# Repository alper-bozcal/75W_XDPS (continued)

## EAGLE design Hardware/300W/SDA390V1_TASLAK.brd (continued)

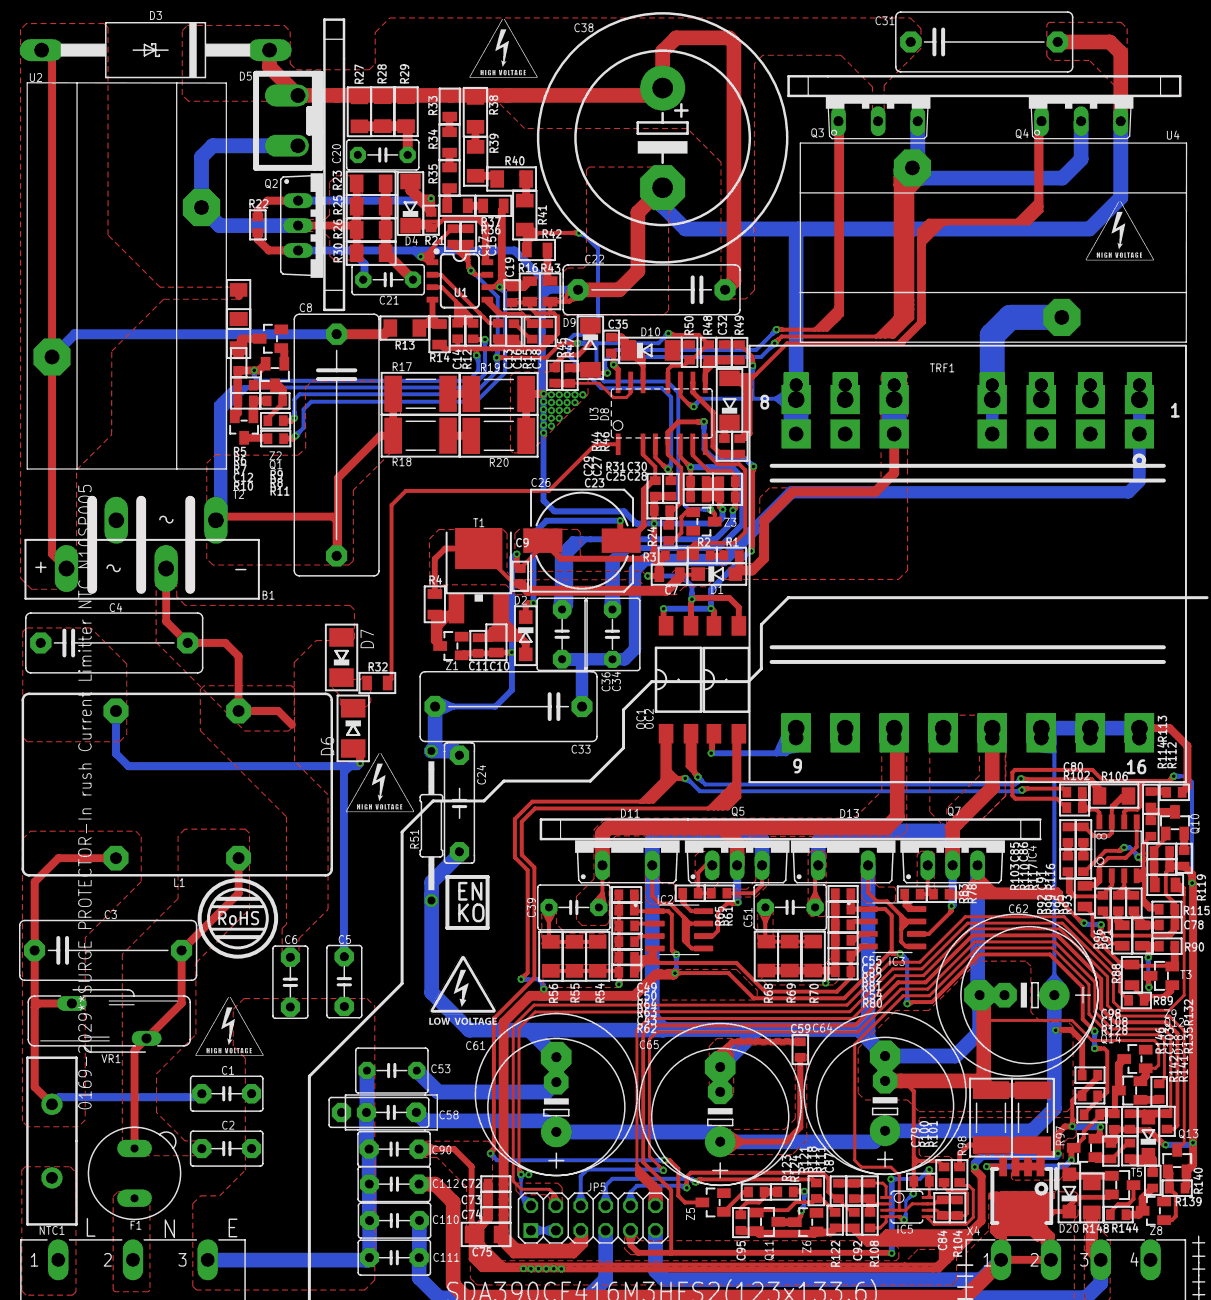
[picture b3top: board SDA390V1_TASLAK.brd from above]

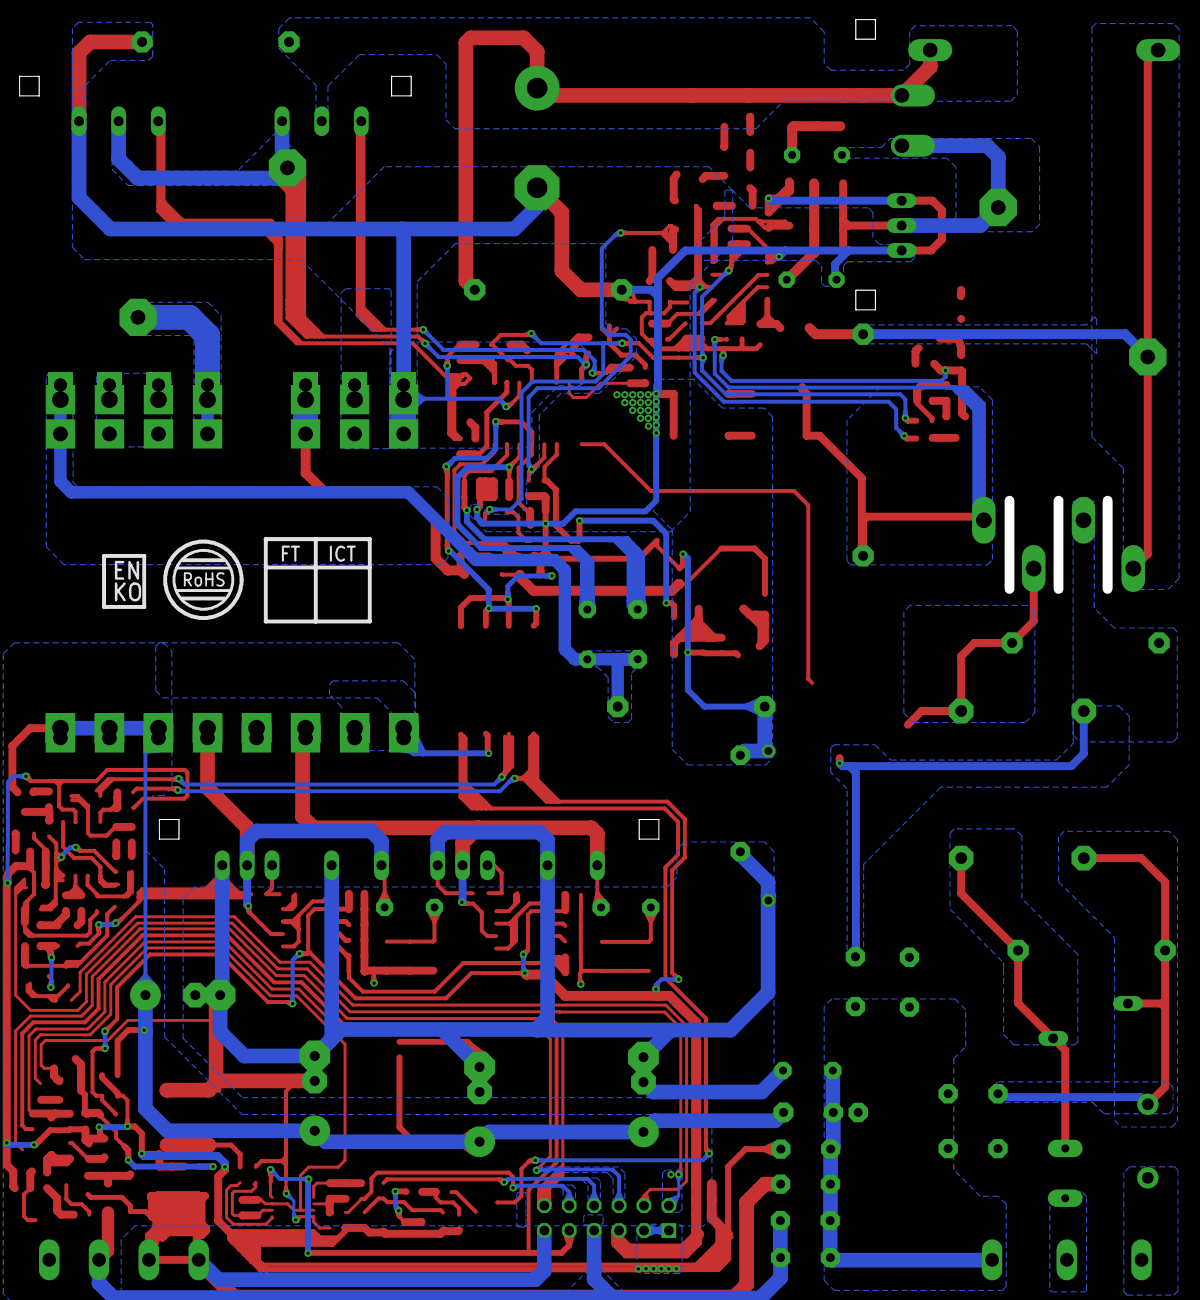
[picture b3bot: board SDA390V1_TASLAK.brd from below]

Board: 3 copper layers, 246 parts (3 on the bottom side), 127 nets.

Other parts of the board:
U$1, U$5: EN-KO_AMLEMI
U$2, U$4: ROHS
U$3: FT-ICT

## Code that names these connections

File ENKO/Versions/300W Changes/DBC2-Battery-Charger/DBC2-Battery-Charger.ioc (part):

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Mcu.Name=STM32F072C(8-B)Tx
Mcu.Package=LQFP48
Mcu.UserName=STM32F072C8Tx
PA0.GPIOParameters=GPIO_Label
PA0.GPIO_Label=VBAT_ADC
PA0.Mode=IN0
PA0.Signal=ADC_IN0
PA1.GPIOParameters=GPIO_Label
PA1.GPIO_Label=VOUT+_ADC
PA1.Mode=IN1
PA1.Signal=ADC_IN1
PA11.Mode=Device
PA11.Signal=USB_DM
PA12.Mode=Device
PA12.Signal=USB_DP
PA13.Mode=Serial_Wire
PA13.Signal=SYS_SWDIO
PA14.Mode=Serial_Wire
PA14.Signal=SYS_SWCLK
PA2.GPIOParameters=GPIO_Label
PA2.GPIO_Label=PT100_ADC
PA2.Mode=IN2
PA2.Signal=ADC_IN2
PA3.GPIOParameters=GPIO_Label
PA3.GPIO_Label=CUT_OFF_OUTPUT
PA3.Signal=GPIO_Output
PA4.GPIOParameters=GPIO_Label
PA4.GPIO_Label=OVER_VOLT
PA4.Signal=GPIO_Input
PA5.GPIOParameters=GPIO_Label
PA5.GPIO_Label=RELAY_OP
PA5.Signal=GPIO_Output
PA6.GPIOParameters=GPIO_Label
PA6.GPIO_Label=V_PWM
PA6.Signal=S_TIM3_CH1
PA7.GPIOParameters=GPIO_Label
PA7.GPIO_Label=I_PWM
PA7.Signal=S_TIM3_CH2
PA8.GPIOParameters=GPIO_Label
PA8.GPIO_Label=TP4
PA8.Signal=GPIO_Output
PB0.GPIOParameters=GPIO_Label
PB0.GPIO_Label=I_OUT_ADC
PB0.Mode=IN8
PB0.Signal=ADC_IN8
PB1.GPIOParameters=GPIO_Label
PB1.GPIO_Label=V_NTC_ADC
PB1.Mode=IN9
PB1.Signal=ADC_IN9
PB10.GPIOParameters=GPIO_Label
PB10.GPIO_Label=TP1
PB10.Signal=GPIO_Output
PB11.GPIOParameters=GPIO_Label
PB11.GPIO_Label=TP2
PB11.Signal=GPIO_Output
PB12.GPIOParameters=GPIO_Label
PB12.GPIO_Label=LED_G
PB12.Signal=GPIO_Output
PB13.GPIOParameters=GPIO_Label
PB13.GPIO_Label=LED_B
PB13.Signal=GPIO_Output
PB14.GPIOParameters=GPIO_Label
PB14.GPIO_Label=LED_R
PB14.Signal=GPIO_Output
PB15.GPIOParameters=GPIO_Label
PB15.GPIO_Label=TP5
PB15.Signal=GPXTI15
PB2.GPIOParameters=GPIO_Label
PB2.GPIO_Label=OUTPUT_REVERSE
PB2.Signal=GPIO_Input
PB3.GPIOParameters=GPIO_Label
PB3.GPIO_Label=JTDO
PB3.Signal=GPIO_Input
PB8.Mode=CAN_Activate
PB8.Signal=CAN_RX
PB9.Mode=CAN_Activate
PB9.Signal=CAN_TX
PC13.GPIOParameters=GPIO_Label
PC13.GPIO_Label=BOOST_INP
PC13.Signal=GPXTI13
RCC.SYSCLKFreq_VALUE=48000000
RCC.SYSCLKSource=RCC_SYSCLKSOURCE_HSI48
board=custom

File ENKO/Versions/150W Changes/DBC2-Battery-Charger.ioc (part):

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Mcu.Name=STM32F072C(8-B)Tx
Mcu.Package=LQFP48
Mcu.UserName=STM32F072C8Tx
PA0.GPIOParameters=GPIO_Label
PA0.GPIO_Label=V_NTC_ADC
PA0.Mode=IN0
PA0.Signal=ADC_IN0
PA1.GPIOParameters=GPIO_Label
PA1.GPIO_Label=PT100_ADC
PA1.Mode=IN1
PA1.Signal=ADC_IN1
PA11.Mode=Device
PA11.Signal=USB_DM
PA12.Mode=Device
PA12.Signal=USB_DP
PA13.Mode=Serial_Wire
PA13.Signal=SYS_SWDIO
PA14.Mode=Serial_Wire
PA14.Signal=SYS_SWCLK
PA15.GPIOParameters=GPIO_Label
PA15.GPIO_Label=OVER_VOLT
PA15.Signal=GPIO_Output
PA2.GPIOParameters=GPIO_Label
PA2.GPIO_Label=RELAY_OP
PA2.Signal=GPIO_Output
PA3.GPIOParameters=GPIO_Label
PA3.GPIO_Label=VBAT_ADC
PA3.Mode=IN3
PA3.Signal=ADC_IN3
PA4.GPIOParameters=GPIO_Label
PA4.GPIO_Label=VOUT+_ADC
PA4.Mode=IN4
PA4.Signal=ADC_IN4
PA5.GPIOParameters=GPIO_Label,GPIO_ModeDefaultEXTI
PA5.GPIO_Label=BOOST_INP
PA5.GPIO_ModeDefaultEXTI=GPIO_MODE_IT_RISING_FALLING
PA5.Signal=GPXTI5
PA6.GPIOParameters=GPIO_Label
PA6.GPIO_Label=CUT_OFF_OUTPUT
PA6.Signal=GPIO_Output
PA7.GPIOParameters=GPIO_Label
PA7.GPIO_Label=I_OUT_ADC
PA7.Mode=IN7
PA7.Signal=ADC_IN7
PB0.GPIOParameters=GPIO_Label
PB0.GPIO_Label=I_PWM
PB0.Signal=S_TIM3_CH3
PB1.GPIOParameters=GPIO_Label
PB1.GPIO_Label=V_PWM
PB1.Signal=S_TIM3_CH4
PB15.GPIOParameters=GPIO_Label
PB15.GPIO_Label=TP4
PB15.Signal=GPXTI15
PB3.GPIOParameters=GPIO_Label
PB3.GPIO_Label=JTDO
PB3.Signal=GPIO_Input
PB4.GPIOParameters=GPIO_Label
PB4.GPIO_Label=LED_G
PB4.Signal=GPIO_Output
PB5.GPIOParameters=GPIO_Label
PB5.GPIO_Label=LED_B
PB5.Signal=GPIO_Output
PB6.GPIOParameters=GPIO_Label
PB6.GPIO_Label=LED_R
PB6.Signal=GPIO_Output
PB8.Mode=CAN_Activate
PB8.Signal=CAN_RX
PB9.Mode=CAN_Activate
PB9.Signal=CAN_TX
RCC.SYSCLKFreq_VALUE=48000000
RCC.SYSCLKSource=RCC_SYSCLKSOURCE_HSI48
board=custom

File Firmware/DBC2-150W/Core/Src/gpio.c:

/* USER CODE BEGIN Header */
/* USER CODE END Header */

/* Includes ------------------------------------------------------------------*/
#include "gpio.h"

/* USER CODE BEGIN 0 */
/* USER CODE END 0 */

/*----------------------------------------------------------------------------*/
/* Configure GPIO                                                             */
/*----------------------------------------------------------------------------*/
/* USER CODE BEGIN 1 */
/* USER CODE END 1 */

/** Configure pins as
        * Analog
        * Input
        * Output
        * EVENT_OUT
        * EXTI
        * Free pins are configured automatically as Analog (this feature is enabled through
        * the Code Generation settings)
*/
void MX_GPIO_Init(void)
{

  GPIO_InitTypeDef GPIO_InitStruct = {0};

  /* GPIO Ports Clock Enable */
  __HAL_RCC_GPIOC_CLK_ENABLE();
  __HAL_RCC_GPIOF_CLK_ENABLE();
  __HAL_RCC_GPIOA_CLK_ENABLE();
  __HAL_RCC_GPIOB_CLK_ENABLE();

  /*Configure GPIO pin Output Level */
  HAL_GPIO_WritePin(GPIOA, RELAY_OP_Pin|CUT_OFF_OUTPUT_Pin|OVER_VOLT_Pin, GPIO_PIN_RESET);

  /*Configure GPIO pin Output Level */
  HAL_GPIO_WritePin(GPIOB, TP4_Pin|LED_G_Pin|LED_B_Pin|LED_R_Pin, GPIO_PIN_RESET);

  /*Configure GPIO pins : PC13 PC14 PC15 */
  GPIO_InitStruct.Pin = GPIO_PIN_13|GPIO_PIN_14|GPIO_PIN_15;
  GPIO_InitStruct.Mode = GPIO_MODE_ANALOG;
  GPIO_InitStruct.Pull = GPIO_NOPULL;
  HAL_GPIO_Init(GPIOC, &GPIO_InitStruct);

  /*Configure GPIO pins : PF0 PF1 */
  GPIO_InitStruct.Pin = GPIO_PIN_0|GPIO_PIN_1;
  GPIO_InitStruct.Mode = GPIO_MODE_ANALOG;
  GPIO_InitStruct.Pull = GPIO_NOPULL;
  HAL_GPIO_Init(GPIOF, &GPIO_InitStruct);

  /*Configure GPIO pins : PAPin PAPin PAPin */
  GPIO_InitStruct.Pin = RELAY_OP_Pin|CUT_OFF_OUTPUT_Pin|OVER_VOLT_Pin;
  GPIO_InitStruct.Mode = GPIO_MODE_OUTPUT_PP;
  GPIO_InitStruct.Pull = GPIO_NOPULL;
  GPIO_InitStruct.Speed = GPIO_SPEED_FREQ_LOW;
  HAL_GPIO_Init(GPIOA, &GPIO_InitStruct);

  /*Configure GPIO pin : PtPin */
  GPIO_InitStruct.Pin = BOOST_INP_Pin;
  GPIO_InitStruct.Mode = GPIO_MODE_IT_RISING_FALLING;
  GPIO_InitStruct.Pull = GPIO_NOPULL;
  HAL_GPIO_Init(BOOST_INP_GPIO_Port, &GPIO_InitStruct);

  /*Configure GPIO pins : PB2 PB10 PB11 PB12
                           PB13 PB14 PB7 */
  GPIO_InitStruct.Pin = GPIO_PIN_2|GPIO_PIN_10|GPIO_PIN_11|GPIO_PIN_12
                          |GPIO_PIN_13|GPIO_PIN_14|GPIO_PIN_7;
  GPIO_InitStruct.Mode = GPIO_MODE_ANALOG;
  GPIO_InitStruct.Pull = GPIO_NOPULL;
  HAL_GPIO_Init(GPIOB, &GPIO_InitStruct);

  /*Configure GPIO pins : PBPin PBPin PBPin PBPin */
  GPIO_InitStruct.Pin = TP4_Pin|LED_G_Pin|LED_B_Pin|LED_R_Pin;
  GPIO_InitStruct.Mode = GPIO_MODE_OUTPUT_PP;
  GPIO_InitStruct.Pull = GPIO_NOPULL;
  GPIO_InitStruct.Speed = GPIO_SPEED_FREQ_LOW;
  HAL_GPIO_Init(GPIOB, &GPIO_InitStruct);

  /*Configure GPIO pins : PA8 PA9 PA10 */
  GPIO_InitStruct.Pin = GPIO_PIN_8|GPIO_PIN_9|GPIO_PIN_10;
  GPIO_InitStruct.Mode = GPIO_MODE_ANALOG;
  GPIO_InitStruct.Pull = GPIO_NOPULL;
  HAL_GPIO_Init(GPIOA, &GPIO_InitStruct);

  /*Configure GPIO pin : PtPin */
  GPIO_InitStruct.Pin = JTDO_Pin;
  GPIO_InitStruct.Mode = GPIO_MODE_INPUT;
  GPIO_InitStruct.Pull = GPIO_NOPULL;
  HAL_GPIO_Init(JTDO_GPIO_Port, &GPIO_InitStruct);

  /* EXTI interrupt init*/
  HAL_NVIC_SetPriority(EXTI4_15_IRQn, 2, 0);
  HAL_NVIC_EnableIRQ(EXTI4_15_IRQn);

}

/* USER CODE BEGIN 2 */
/* USER CODE END 2 */
